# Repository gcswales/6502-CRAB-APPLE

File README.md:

# CRAB APPLE - A MINIMAL 6502 COMPUTER

This project was initially intended as a personal project but due to the level of interest I have decided to publish the documentation.

## Introduction

The Crab Apple is a very simple and minimalist computer, as such is ideal for the first-time builder wanting to build their own retro-computer.

Just to clarify; **the system will run most software for the Apple I computer but, due to the minimalist nature of the design, it is NOT hardware compatible with the Apple I.**

Ultimately the Crab Apple is minimum complexity, minimum cost and maximum fun!

## Minimal

The Crab Apple is not emulated and does not use an FPGA; the architecture is fairly standard with the exception of an 8-bit microcontroller which will be explained later.

## Memory

At the heart of the Crab Apple is a 65C02 microprocessor. This is the modern version of the classic 6502 device which has a wider operating frequency (you’ll see why later) and still readily available.

The system has 32k of RAM in the form of a 28-pin static RAM chip. It has a 28-pin 8k of ROM chip; this is an EEPROM rather than the older (and considerably more expensive) EPROMs.

Memory address decoding is achieved with a single 7400 (quad NAND gate) chip. This provides quite a loose decoding of the address space and isn’t very efficient but it does the job.

Memory Map:

|Start Address | End Address | Description |
|-----|-----|-----|
| E000 | FFFF | 8K ROM FOR OS |
| 8000 | DFFF | UART |
| 0000 | 7FFF | 32K RAM |

## UART

This is the biggest *hack*; Rather than use several chips the Crab Apple uses a single low-cost microcontroller to act as an all-in-one serial interface. When used in conjunction with a PC running suitable terminal software the system can display text and receive keyboard input.

The microcontroller used (PIC18F15Q41) runs off an internal oscillator at 64MHz (16MIPS), however it still does not have sufficient speed to access and respond to the 6502 data bus  in real-time. To over-come this the PIC also provides the system clock to the CPU. When the PIC is selected by the data bus it halts the system clock (effectively freezing time for the 6502). This enables the PIC to leisurely read from/write to the data bus, before resuming the system clock. 

Despite this momentary drop in CPU clock speed, this has a negligible affect on performance. The biggest ‘bottle-neck’ in the system is the serial BAUD rate. The PIC is capable of higher BAUD rates than older devices; up to 115200. Additionally the PIC can provide a CPU clock speed up to 4MHz, further boosting performance.

Because of this momentary drop is CPU clock speed it is recommended to only use the modern MOS 65C02 CPU.
At high BAUD rates, especially when downloading software, serial flow control is essential to guard against data loss/corruption. The PIC handles this in two ways;

* The PIC uses Xon/Xoff flow control. It is recommended to have this enables in any terminal software connected to the Crab Apple.

* The PIC uses a 256-byte deep receiver buffer. Some USB-to-TTL serial modules insist on sending their entire packet (32 bytes) despite flow control. Once the PICs buffer is 75% full it issues an Xoff to pause the data. It still has room to receive 64 bytes, so no data is lost. The PIC issues the Xon to resume data once the receive buffer is down to 25% full.

## CPU Clock

To reduce cost the PIC provides a user adjustable system clock. Clock speeds of 1MHz, 2MHz or 4MHz can be selected from the BIOS menu.

## CPU Reset

To reduce board complexity the PIC also provides a clean reset, which is triggered on power-up or by the user pressing the reset button.

## Building

IMPORTANT UPDATE: If using the WDC 6502, pin 1 is not connected to ground. It is used to indicate that an interrupt is happening (for DMA, etc). If using a WDC 6502 it is best to gently 'bend' pin 1 so it does not sit in the DIP contact.

The schematic and PCB have been created using KiCAD, these files can be found in the *ELECTRONICS* folder.

You can buy the PCB from here: <a href="https://www.pcbway.com/project/shareproject/MINIMAL_6502_SINGLE_BOARD_COMPUTER_CRAB_APPLE_I_d3186ce3.html">PCBWay</a>

The bill of material (BOM) uses <a href="https://www.mouser.co.uk/">Mouser</a> codes and prices as on January 2023, however buying from <a href="https://www.ebay.co.uk/">Ebay</a> will considerably reduce the cost (buyer be ware!).

I recommend using IC sockets so the ICs can be removed (especially the ROM for programming). As with any build; start with the smallest (profile) parts and build up to the taller components; resistors, capacitors, button, IC sockets, serial connector then LED last.

## PIC18 Programming

To program the PIC18F you will need a PICKIT4 programmer, I do not think the PICKIT3 is compatible with the newer PICs. I cannot comment on the PICKIT3.5 clones.

You will also need to download and install the free programming IDE MPLABX: <a href="https://www.microchip.com/en-us/tools-resources/develop/mplab-x-ide"> MPLABX</a>

The source code is written in XC8, the compiler can be downloaded for free: <a href="https://www.microchip.com/en-us/tools-resources/develop/mplab-xc-compilers">XC8</a>

If you prefer to keep it simple the HEX code is here: <a href="https://github.com/gcswales/6502-CRAB-APPLE/blob/main/FIRMWARE/CRAB_APPLE_BIOS.X/dist/default/production/CRAB_APPLE_BIOS.X.production.hex">HEX</a>

The PIC18 can be programmed in-circuit by connecting to the serial connector on the board. You will need to access the PICKIT4 options and enable the PICKIT4 to provide 5V power to the board.

| SERIAL PIN | PICKIT4 PIN |
|--------|---------|
| 1** |  |
| 2 | ICSPDATA |
| 3 | MCLR |
| 4 | Vdd |
| 5 | ICSPCLK |
| 6 | GND |

** PIN1 is the pin closest to the silk screen legend ‘J1’.

## ROM Programming

You will need a suitable EEPROM programmer in order to program the EEPROM. There are many ROM images on line, I would recommend ensuring that whatever image you go for it has the obligatory WOZMON memory monitor in it. You will need to ensure the ROM image you use is targetted at the address range E000 – FFFF.

## Serial Connection

The serial connections with a USB/TTL module are as follows:-
| SERIAL PIN | PICKIT4 PIN |
|--------|---------|
| 1** | DTR |
| 2 | RX |
| 3 | TX |
| 4 | Vcc |
| 5 | CTS |
| 6 | GND |

** PIN1 is the pin closest to the silk screen legend ‘J1’.

**IMPORTANT: POWER TO THE CRAB APPLE IS PROVIDED BY THE USB/TTL MODULE. ENSURE THE POWER JUMPER ON THE MODULE IS SET TO 5V AS IN THE IMAGE ABOVE.**

The default BAUD rate is 19200. This can be modified by accessing the Crab Apple BIOS menu.
To ensure data integrity it is recommended to enable software flow control (Xon/Xoff).
A lot of Apple I software only sends carriage return (CR) without line feed (LF). For text to display correctly you may need to modify the setting in your serial terminal software to *imply* a LF for every CR received.

## BIOS Menu

The Crab Apple BIOS menu is activated by pressing the space bar during the boot screen while the animated cursor is *rotating*. The menu enables the user to configure the CPU speed, serial BAUD rate and default text colour.

Here is a short video (no sound) showing the BIOS menu in action: <a href="https://youtube.com/shorts/APpxrt6QOSg">YouTube Video</a>

## Thank you

I hope you enjoy the Crab Apple. Please  post photos and comments online and feel free to modify/improve the system.

Best regards,

*Geoffrey*

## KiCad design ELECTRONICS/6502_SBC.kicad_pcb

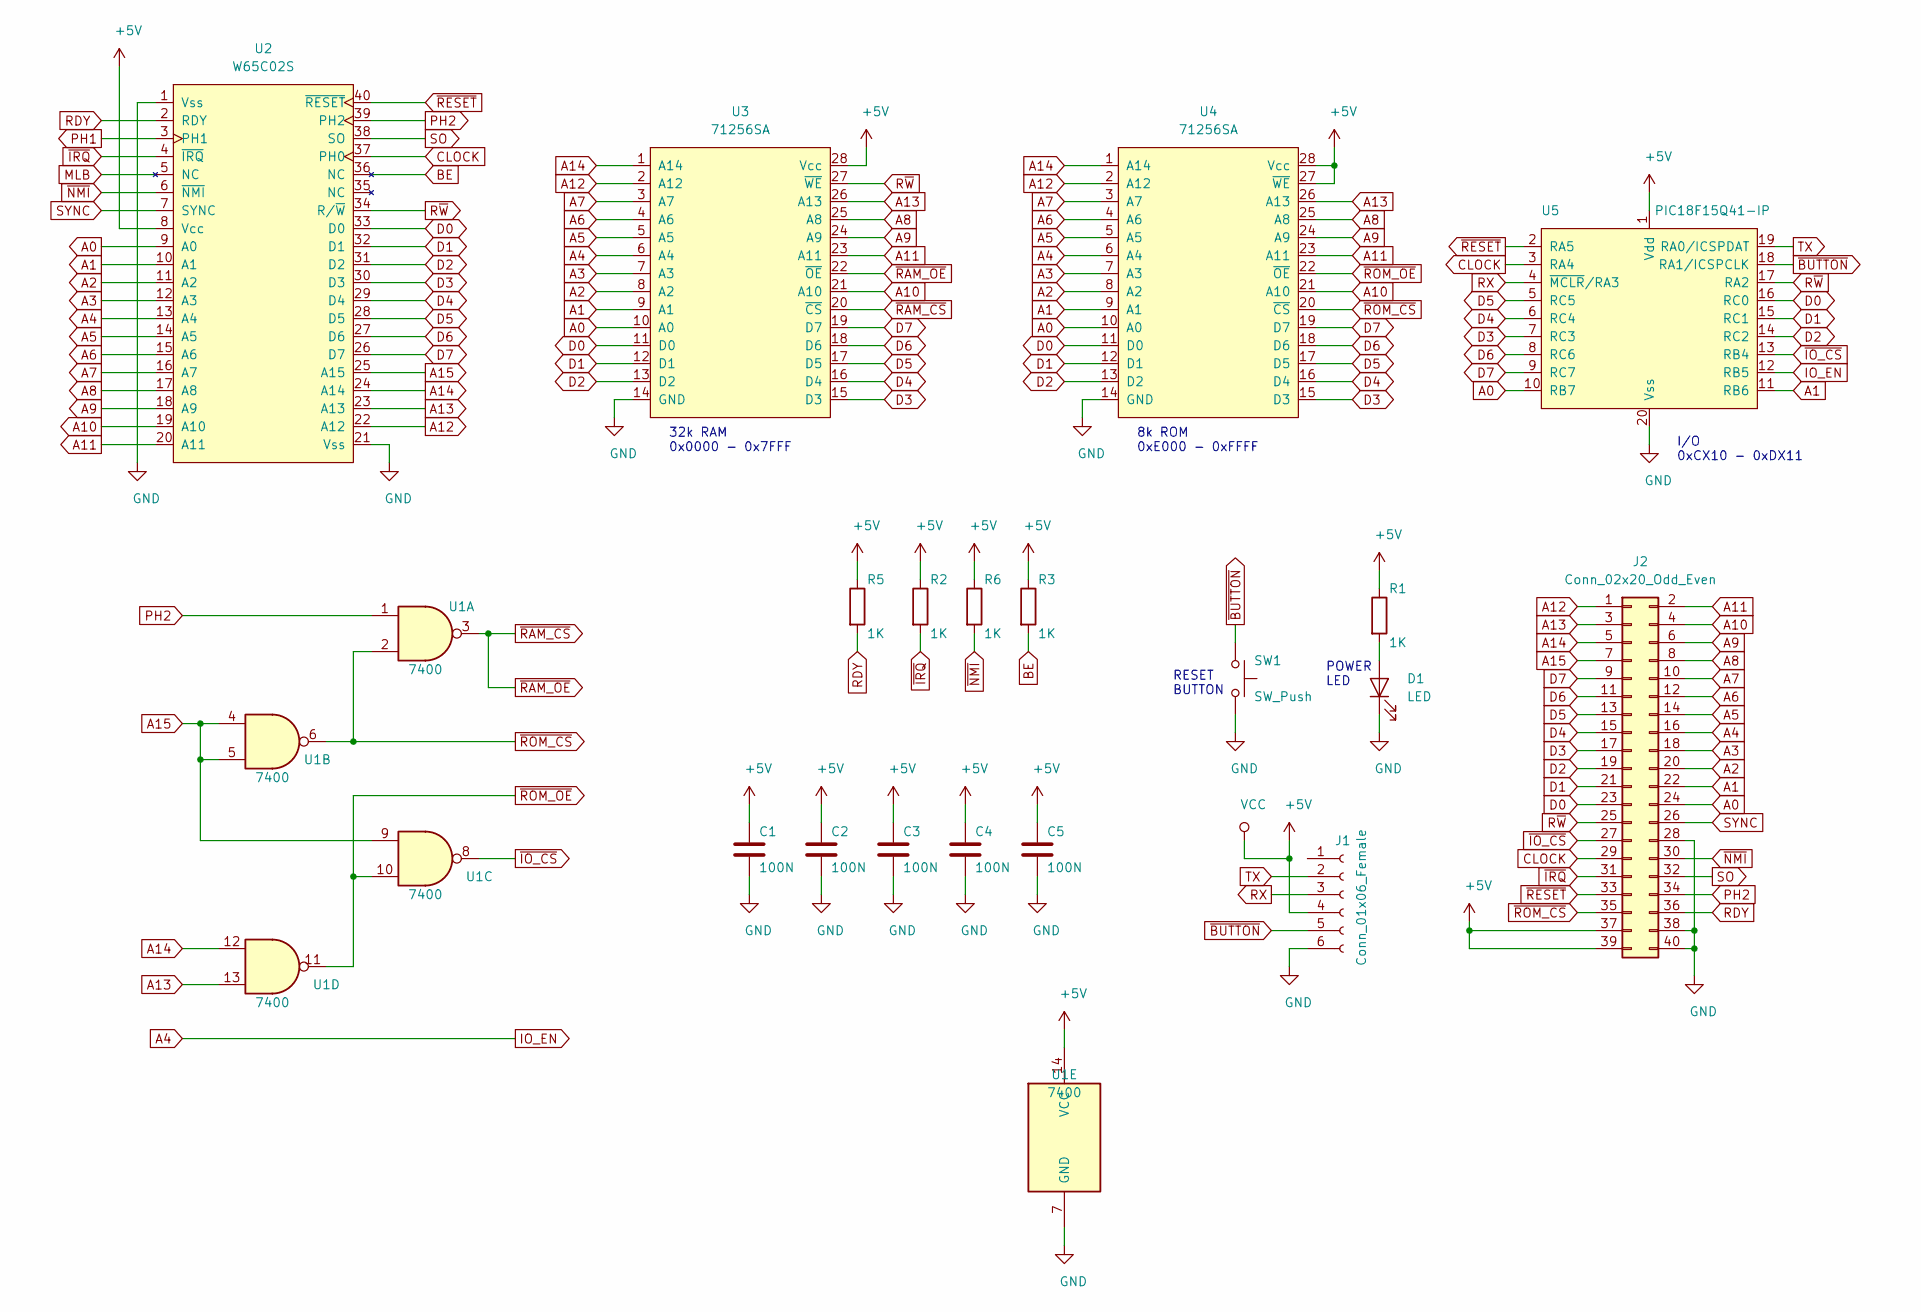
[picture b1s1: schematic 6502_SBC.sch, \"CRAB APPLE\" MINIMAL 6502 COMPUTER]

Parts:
C1, C2, C3, C4, C5: 100N; C_Disc_D5.0mm_W2.5mm_P2.50mm
D1: LED; LED_D5.0mm
J1: Conn_01x06_Female; PinSocket_1x06_P2.54mm_Vertical
J2: Conn_02x20_Odd_Even; IDC-Header_2x20_P2.54mm_Vertical
R1, R2, R3, R5, R6: 1K; R_Axial_DIN0207_L6.3mm_D2.5mm_P10.16mm_Horizontal
SW1: SW_Push; SW_PUSH_6mm
U1: 7400; DIP-14_W7.62mm_Socket_LongPads
U2: W65C02S; DIP-40_W15.24mm_Socket_LongPads
U3, U4: 71256SA; DIP-28_W15.24mm_Socket_LongPads
U5: PIC18F15Q41-IP; DIP-20_W7.62mm_Socket_LongPads

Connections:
+5V: C1.1, C2.1, C3.1, C4.1, C5.1, J1.4, J2.37, J2.39, R1.1, R2.1, R3.1, R5.1, R6.1, U1.14 (VCC), U2.8 (Vcc), U3.28 (Vcc), U4.27 (~WE~), U4.28 (Vcc), U5.1 (Vdd)
A0: J2.24, U2.9 (A0), U3.10 (A0), U4.10 (A0), U5.10 (RB7)
A1: J2.22, U2.10 (A1), U3.9 (A1), U4.9 (A1), U5.11 (RB6)
A2: J2.20, U2.11 (A2), U3.8 (A2), U4.8 (A2)
A3: J2.18, U2.12 (A3), U3.7 (A3), U4.7 (A3)
A4: J2.16, U2.13 (A4), U3.6 (A4), U4.6 (A4), U5.12 (RB5)
A5: J2.14, U2.14 (A5), U3.5 (A5), U4.5 (A5)
A6: J2.12, U2.15 (A6), U3.4 (A6), U4.4 (A6)
A7: J2.10, U2.16 (A7), U3.3 (A7), U4.3 (A7)
A8: J2.8, U2.17 (A8), U3.25 (A8), U4.25 (A8)
A9: J2.6, U2.18 (A9), U3.24 (A9), U4.24 (A9)
A10: J2.4, U2.19 (A10), U3.21 (A10), U4.21 (A10)
A11: J2.2, U2.20 (A11), U3.23 (A11), U4.23 (A11)
A12: J2.1, U2.22 (A12), U3.2 (A12), U4.2 (A12)
A13: J2.3, U1.13, U2.23 (A13), U3.26 (A13), U4.26 (A13)
A14: J2.5, U1.12, U2.24 (A14), U3.1 (A14), U4.1 (A14)
A15: J2.7, U1.4, U1.5, U1.9, U2.25 (A15)
BE: R3.2, U2.36 (NC)
CLOCK: J2.29, U2.37 (PH0), U5.3 (RA4)
D0: J2.23, U2.33 (D0), U3.11 (D0), U4.11 (D0), U5.16 (RC0)
D1: J2.21, U2.32 (D1), U3.12 (D1), U4.12 (D1), U5.15 (RC1)
D2: J2.19, U2.31 (D2), U3.13 (D2), U4.13 (D2), U5.14 (RC2)
D3: J2.17, U2.30 (D3), U3.15 (D3), U4.15 (D3), U5.7 (RC3)
D4: J2.15, U2.29 (D4), U3.16 (D4), U4.16 (D4), U5.6 (RC4)
D5: J2.13, U2.28 (D5), U3.17 (D5), U4.17 (D5), U5.5 (RC5)
D6: J2.11, U2.27 (D6), U3.18 (D6), U4.18 (D6), U5.8 (RC6)
D7: J2.9, U2.26 (D7), U3.19 (D7), U4.19 (D7), U5.9 (RC7)
GND: C1.2, C2.2, C3.2, C4.2, C5.2, D1.1 (K), J1.6, J2.28, J2.38, J2.40, SW1.2, U1.7 (GND), U2.1 (Vss), U2.21 (Vss), U3.14 (GND), U4.14 (GND), U5.20 (Vss)
unnamed: D1.2 (A), R1.2
PH2: J2.34, U1.1, U2.39 (PH2)
RDY: J2.36, R5.2, U2.2 (RDY)
RX: J1.3, U5.4 (~MCLR~/RA3)
R~W~: J2.25, U2.34 (R/~W~), U3.27 (~WE~), U5.17 (RA2)
SO: J2.32, U2.38 (SO)
SYNC: J2.26, U2.7 (SYNC)
TX: J1.2, U5.19 (RA0/ICSPDAT)
~BUTTON~: J1.5, SW1.1, U5.18 (RA1/ICSPCLK)
~IO_CS~: J2.27, U1.8, U5.13 (RB4)
~IRQ~: J2.31, R2.2, U2.4 (~IRQ)
~NMI~: J2.30, R6.2, U2.6 (~NMI)
~RAM_CS~: U1.3, U3.20 (~CS~), U3.22 (~OE~)
~RESET~: J2.33, U2.40 (~RESET~), U5.2 (RA5)
~ROM_CS~: J2.35, U1.2, U1.6, U4.20 (~CS~)
~ROM_OE~: U1.10, U1.11, U4.22 (~OE~)

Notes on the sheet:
32k RAM 0x0000 - 0x7FFF
8k ROM 0xE000 - 0xFFFF
I/O 0xCX10 - 0xDX11
POWER LED
RESET BUTTON

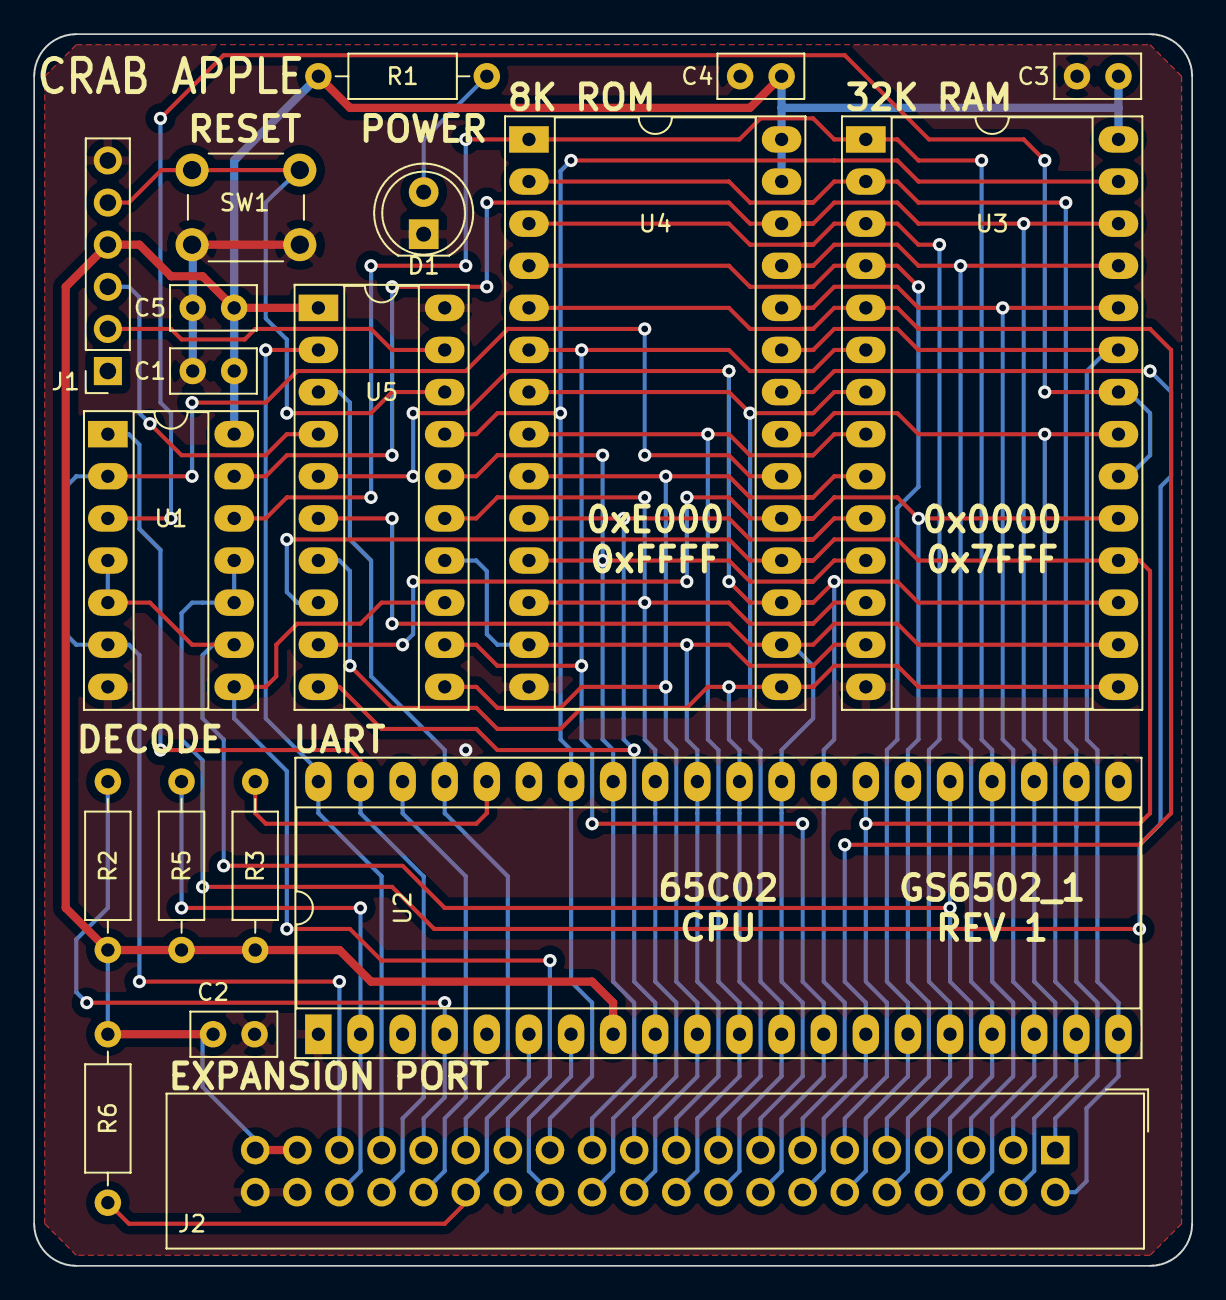
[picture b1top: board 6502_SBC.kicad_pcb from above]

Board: 2 copper layers, 69.9 x 74.3 mm, 19 parts (0 on the bottom side), 44 nets.

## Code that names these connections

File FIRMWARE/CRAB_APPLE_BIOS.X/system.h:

//*************************************************************
//***	FILE:		SYSTEM.H								***
//***	DATE:		28/09/21								***
//***	AUTHOR:		GEOFFREY SWALES							***
//***	VERSION:	V1.0									***
//*************************************************************
//***	DESCRIPTION:										***
//*************************************************************
//***	VERSION TRACK:										***
//***	V0.1: INITIAL DEVELOPMENT VERSION					***
//*************************************************************
//
//
//*************************************************************
//*** REDEFINITION BLOCKING ***********************************
//*************************************************************
//
#ifndef SYSTEM_H
#define	SYSTEM_H
//
//*************************************************************
//*** C++ COMPATABILITY ***************************************
//*************************************************************
//
#ifdef __cplusplus
extern "C" {
#endif
//
//*************************************************************
//*** INCLUDE USEFUL COMPILER DEFINTIONS **********************
//*************************************************************
//
#include <xc.h>												// PIC18F definitions
#include <stdint.h>											// industrial standard variable types
#include <stdbool.h>										// some boolian definitions
//
//*************************************************************
//*** USEFUL DEFINITIONS **************************************
//*************************************************************
//
#define _XTAL_FREQ 64000000									// define system speed
//
#define INTERRUPT_GlobalInterruptHighEnable() (INTCON0bits.GIEH = 1)
#define INTERRUPT_GlobalInterruptHighDisable() (INTCON0bits.GIEH = 0)
#define INTERRUPT_GlobalInterruptLowEnable() (INTCON0bits.GIEL = 1)
#define INTERRUPT_GlobalInterruptLowDisable() (INTCON0bits.GIEL = 0)
//
//*************************************************************
//*** DECLARE PIN NAMES ***************************************
//*************************************************************
// 
// UART TX OUTPUT (DISPLAY)
//
#define	TX_SET			LATAbits.LATA0
#define	TX_GET			PORTAbits.RA0
#define	TX_DIR			TRISAbits.TRISA0
//
// RESET BUTTON INPUT
//
#define	BUTTON_SET		LATAbits.LATA1
#define	BUTTON_GET		PORTAbits.RA1
#define	BUTTON_DIR		TRISAbits.TRISA1
//
// 6502 R/#W INPUT
//
#define	RW_SET			LATAbits.LATA2
#define	RW_GET			PORTAbits.RA2
#define	RW_DIR			TRISAbits.TRISA2
//
// UART RX INPUT (KEYBOARD)
//
#define	RX_SET			LATAbits.LATA3
#define	RX_GET			PORTAbits.RA3
#define	RX_DIR			TRISAbits.TRISA3
//
// CPU CLOCK OUTPUT
//
#define	CLOCK_SET		LATAbits.LATA4
#define	CLOCK_GET		PORTAbits.RA4
#define	CLOCK_DIR		TRISAbits.TRISA4
//
// CPU RESET OUTPUT
//
#define	RESET_SET		LATAbits.LATA5
#define	RESET_GET		PORTAbits.RA5
#define	RESET_DIR		TRISAbits.TRISA5
//
// OUT CHIP SELECT ACTIVE LOW INPUT
//
#define	IO_CS_SET		LATBbits.LATB4
#define	IO_CS_GET		PORTBbits.RB4
#define	IO_CS_DIR		TRISBbits.TRISB4
//
// OUR CHIP ENABLE ACTIVE HIGH INPUT
//
#define	IO_EN_SET		LATBbits.LATB5
#define	IO_EN_GET		PORTBbits.RB5
#define	IO_EN_DIR		TRISBbits.TRISB5
//
// CPU ADDRESS LINE 1 INPUT
//
#define	A1_SET			LATBbits.LATB6
#define	A1_GET			PORTBbits.RB6
#define	A1_DIR			TRISBbits.TRISB6
//
// CPU ADDRESS LINE 0 INPUT
//
#define	A0_SET			LATBbits.LATB7
#define	A0_GET			PORTBbits.RB7
#define	A0_DIR			TRISBbits.TRISB7
//
// CPU DATA BUS INPUT (8-BITS)
//
#define	DATA_SET		LATC
#define	DATA_GET		PORTC
#define	DATA_DIR		TRISC
//
//*************************************************************
//*** DECLARE NEW STRUCURES ***********************************
//*************************************************************
//  

//
//*************************************************************
//*** DECLARE EXTERNAL VARIABLES ******************************
//*************************************************************
//
	
//
//*************************************************************
//*** PROTOTYPE FUNCTIONS *************************************
//*************************************************************
//
void system_init( void );									// initialise basic hardare
void oscillator_init( void );								// initialise oscillator
void peripheral_disable_init( void );						// initialise peripheral disable module
void pin_init( void );										// initialise pins
void interrupt_init( void );								// initialise vector interrupts
//
//*************************************************************
//*** END C++ COMPATABILITY ***********************************
//*************************************************************
//
#ifdef __cplusplus
}
#endif
//
//*************************************************************
//*** END OF REDEFINITION BLOCKING ****************************
//*************************************************************
//
#endif	

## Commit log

2023-01-16 Create LICENSE
